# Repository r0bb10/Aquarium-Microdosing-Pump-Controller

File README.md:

# Aquarium-Microdosing-Pump-Controller
Software for an ESP8266 base aquarium micro-dosing pump. Controlled through a local webpage. Currently hard-coded to control a single pump, the hardware supports up to four. 

Required Libraries:
Adafruit I2C FRAM Library
Adafruit RTClib
ESPAsyncWebServer
ESPAsyncTCP
NTPClient
ESP8266TimerInterrupt
#Alepiro85 Changelog: ESP_EEPROM by j-watson

Also needed:
Setting up Arduino IDE to support uploading files to SPIFFS: https://randomnerdtutorials.com/install-esp8266-filesystem-uploader-arduino-ide/

Required Hardware:
MB85RC256V I2C FRAM. This is for saving configurations without constantly writing to internal memory to prevent excessive wearing. 
#Alepiro85 Changelog: from version 0.1A: Not necessary, it is possible to save parameters on EEPROM
DS3231 RTC. For keeping track of time if wifi is unavailable. 

Known Problems:
Need to redesign PCB to be smaller and cheaper. Software is hard-coded for a single pump. 
#Alepiro85 Changelog: from Version 0.1B: Software manages 4 pumps control

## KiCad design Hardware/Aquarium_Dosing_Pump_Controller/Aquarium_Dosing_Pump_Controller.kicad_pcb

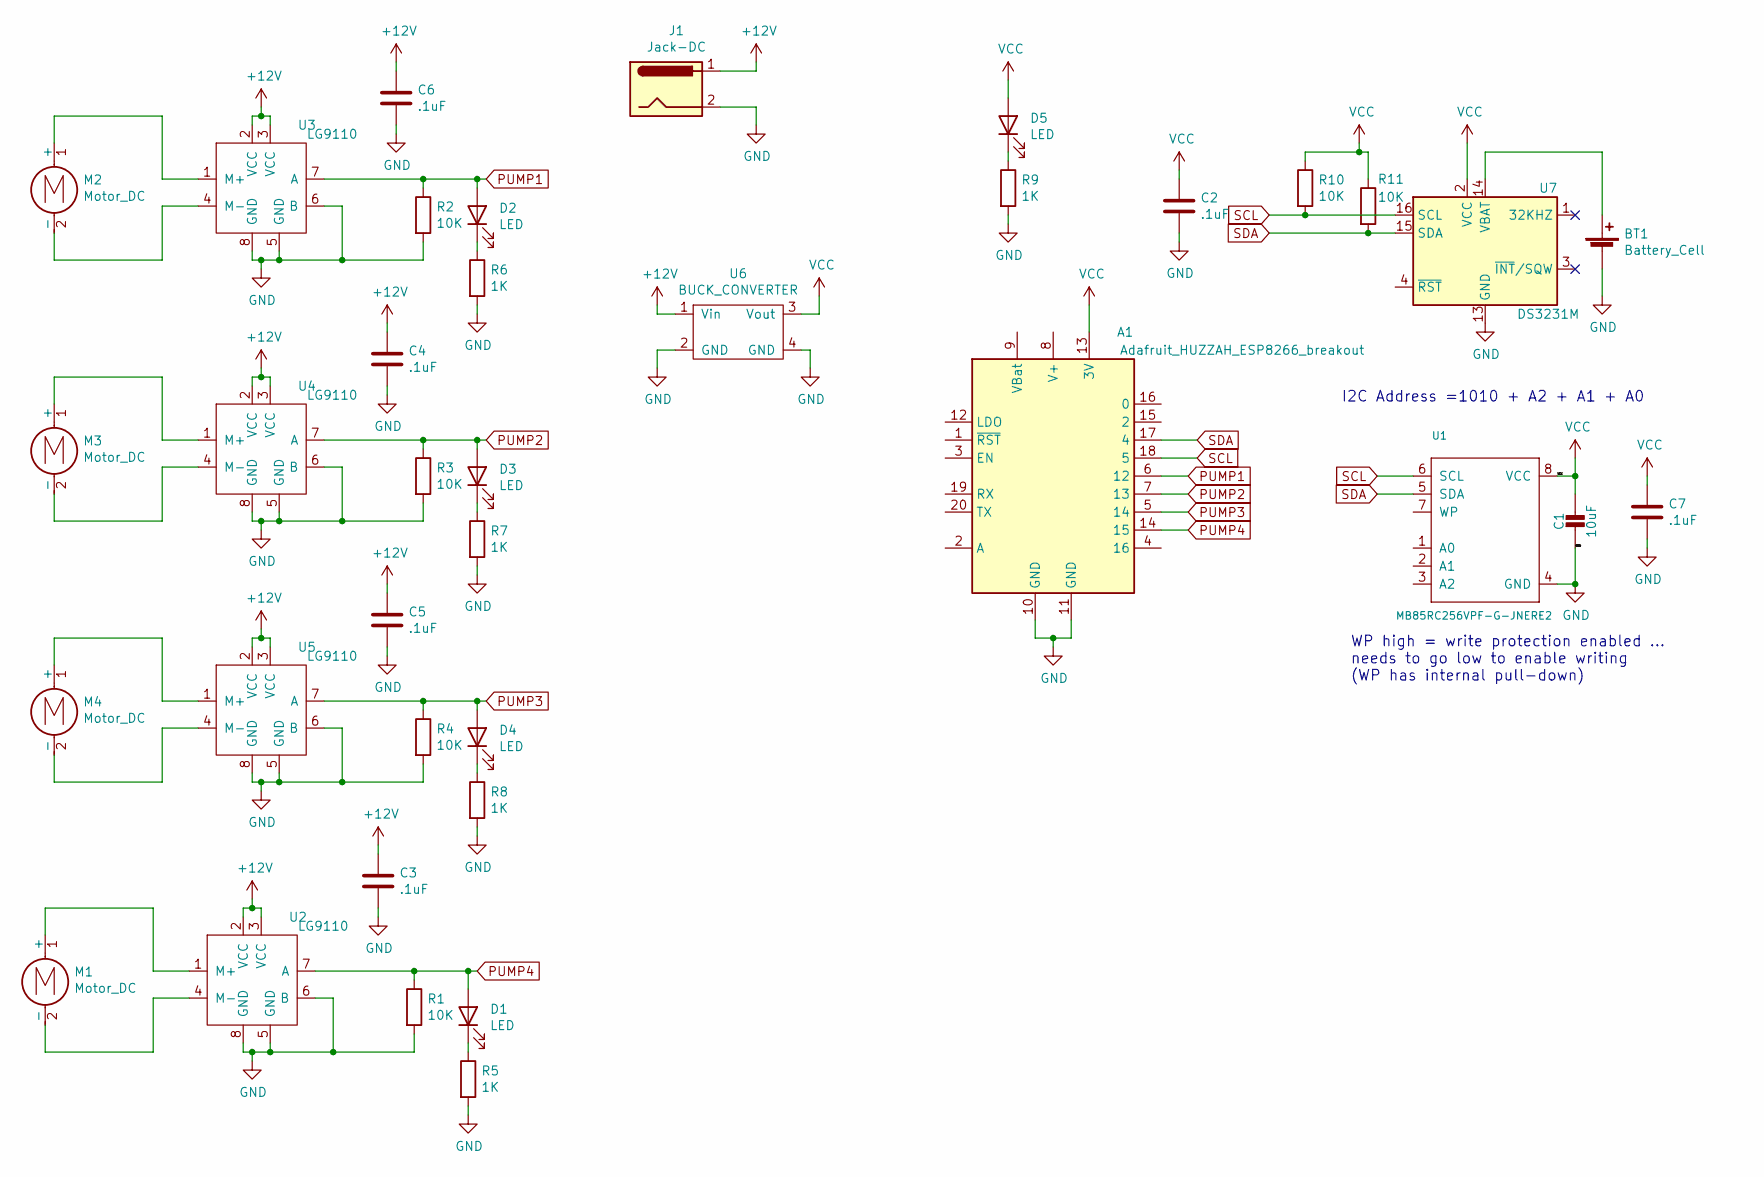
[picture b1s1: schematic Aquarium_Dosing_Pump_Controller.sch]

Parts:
A1: Adafruit_HUZZAH_ESP8266_breakout
BT1: Battery_Cell; CR1220
C1: 10uF; R_1206_3216Metric_Pad1.42x1.75mm_HandSolder
C2, C3, C4, C5, C6, C7: .1uF; R_1206_3216Metric_Pad1.42x1.75mm_HandSolder
D1, D2, D3, D4, D5: LED; LED_1206_3216Metric_Pad1.42x1.75mm_HandSolder
J1: Jack-DC; BarrelJack_Horizontal
M1, M2, M3, M4: Motor_DC; PinHeader_1x02_P2.54mm_Vertical
R1, R2, R3, R4, R10, R11: 10K; R_0603_1608Metric_Pad1.05x0.95mm_HandSolder
R5, R6, R7, R8, R9: 1K; R_0603_1608Metric_Pad1.05x0.95mm_HandSolder
U1: MB85RC256VPF-G-JNERE2; SOIJ-8_5.3x5.3mm_P1.27mm
U2, U3, U4, U5: LG9110; DIP-8_W7.62mm_LongPads
U6: BUCK_CONVERTER; Boost_Footprint
U7: DS3231M; SOIC-16W_7.5x10.3mm_P1.27mm

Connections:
+12V: C3.1, C4.1, C5.1, C6.1, J1.1, U2.2 (VCC), U2.3 (VCC), U3.2 (VCC), U3.3 (VCC), U4.2 (VCC), U4.3 (VCC), U5.2 (VCC), U5.3 (VCC), U6.1 (Vin)
GND: A1.10 (GND), A1.11 (GND), BT1.2 (-), C1.2, C2.2, C3.2, C4.2, C5.2, C6.2, C7.2, J1.2, R1.2, R2.2, R3.2, R4.2, R5.2, R6.2, R7.2, R8.2, R9.2, U1.4 (GND), U2.5 (GND), U2.6 (B), U2.8 (GND), U3.5 (GND), U3.6 (B), U3.8 (GND), U4.5 (GND), U4.6 (B), U4.8 (GND), U5.5 (GND), U5.6 (B), U5.8 (GND), U6.2 (GND), U6.4 (GND), U7.5 (GND), U7.6 (GND), U7.7 (GND), U7.8 (GND), U7.9 (GND), U7.10 (GND), U7.11 (GND), U7.12 (GND), U7.13 (GND)
unnamed: BT1.1 (+), U7.14 (VBAT)
unnamed: D1.1 (K), R5.1
unnamed: D2.1 (K), R6.1
unnamed: D3.1 (K), R7.1
unnamed: D4.1 (K), R8.1
unnamed: D5.1 (K), R9.1
unnamed: M1.1 (+), U2.1 (M+)
unnamed: M1.2 (-), U2.4 (M-)
unnamed: M2.1 (+), U3.1 (M+)
unnamed: M2.2 (-), U3.4 (M-)
unnamed: M3.1 (+), U4.1 (M+)
unnamed: M3.2 (-), U4.4 (M-)
unnamed: M4.1 (+), U5.1 (M+)
unnamed: M4.2 (-), U5.4 (M-)
PUMP1: A1.6 (12), D2.2 (A), R2.1, U3.7 (A)
PUMP2: A1.7 (13), D3.2 (A), R3.1, U4.7 (A)
PUMP3: A1.5 (14), D4.2 (A), R4.1, U5.7 (A)
PUMP4: A1.14 (15), D1.2 (A), R1.1, U2.7 (A)
SCL: A1.18 (5), R10.2, U1.6 (SCL), U7.16 (SCL)
SDA: A1.17 (4), R11.2, U1.5 (SDA), U7.15 (SDA)
VCC: A1.13 (3V), C1.1, C2.1, C7.1, D5.2 (A), R10.1, R11.1, U1.8 (VCC), U6.3 (Vout), U7.2 (VCC)

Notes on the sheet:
I2C Address =1010 + A2 + A1 + A0
WP high = write protection enabled ... needs to go low to enable writing~ (WP has internal pull-down)

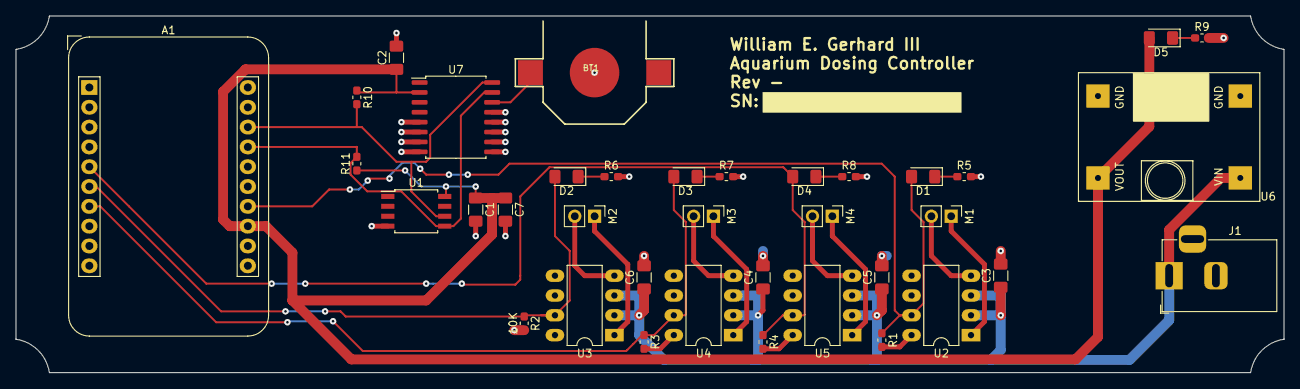
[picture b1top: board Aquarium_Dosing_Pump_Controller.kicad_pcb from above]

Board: 2 copper layers, 162.6 x 45.7 mm, 37 parts (0 on the bottom side), 23 nets.

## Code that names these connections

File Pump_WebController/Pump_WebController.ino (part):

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#define SETMEMADD 1000

// Set PUMP GPIO
const int gpio_PUMP1 = 12;
const int gpio_PUMP2 = 13;
const int gpio_PUMP3 = 14;
const int gpio_PUMP4 = 15;
const int pinReset = 16;
const int pinButton = 0;

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    EEPROM.begin(EEPROM_SIZE);
  #endif

  pinMode(gpio_PUMP1, OUTPUT);
  digitalWrite(gpio_PUMP1, LOW);
  pinMode(gpio_PUMP2, OUTPUT);
  digitalWrite(gpio_PUMP2, LOW);
  pinMode(gpio_PUMP3, OUTPUT);
  digitalWrite(gpio_PUMP3, LOW);
  pinMode(gpio_PUMP4, OUTPUT);
  digitalWrite(gpio_PUMP4, LOW);  

  WiFiManager wifiManager;
  wifiManager.setAPCallback(configModeCallback);
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    Serial.println(F("Can't set ITimer correctly. Select another frequency or interval"));
  }
  
  pump1 = loadPump(P1MEMADD,gpio_PUMP1);
  pump2 = loadPump(P2MEMADD,gpio_PUMP2);
  pump3 = loadPump(P3MEMADD,gpio_PUMP3);
  pump4 = loadPump(P4MEMADD,gpio_PUMP4);
  
  #ifdef EXT_MEMORY
    fram.read(SETMEMADD, tempSettings);
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  server.on("/cal1on", HTTP_GET, [] (AsyncWebServerRequest * request)
  {
    pump1.programEnable = false;
    digitalWrite(pump1.motor_GPIO, HIGH);
    startMillis = millis();
    #ifdef DEBUG
      Serial.println("ON");
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  server.on("/cal2on", HTTP_GET, [] (AsyncWebServerRequest * request)
  {
    pump2.programEnable = false;
    digitalWrite(pump2.motor_GPIO, HIGH);
    startMillis = millis();
    request->send(SPIFFS, "/index.html", String(), false);
  });
  server.on("/cal3on", HTTP_GET, [] (AsyncWebServerRequest * request)
  {
    pump3.programEnable = false;
    digitalWrite(pump3.motor_GPIO, HIGH);
    startMillis = millis();
    request->send(SPIFFS, "/index.html", String(), false);
  });
  server.on("/cal4on", HTTP_GET, [] (AsyncWebServerRequest * request)
  {
    pump4.programEnable = false;
    digitalWrite(pump4.motor_GPIO, HIGH);
    startMillis = millis();
    request->send(SPIFFS, "/index.html", String(), false);
  });
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  server.on("/cal1off", HTTP_GET, [] (AsyncWebServerRequest * request)
  {
    pump1.programEnable = true;
    digitalWrite(pump1.motor_GPIO, LOW);
    stopMillis = millis();
    pump1.CAL_pumpmS = (stopMillis - startMillis);
    Serial.println(pump1.CAL_pumpmS);
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  server.on("/cal2off", HTTP_GET, [] (AsyncWebServerRequest * request)
  {
    pump2.programEnable = true;
    digitalWrite(pump2.motor_GPIO, LOW);
    stopMillis = millis();
    pump2.CAL_pumpmS = (stopMillis - startMillis);
    Serial.println(pump2.CAL_pumpmS);
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  server.on("/cal3off", HTTP_GET, [] (AsyncWebServerRequest * request)
  {
    pump3.programEnable = true;
    digitalWrite(pump3.motor_GPIO, LOW);
    stopMillis = millis();
    pump3.CAL_pumpmS = (stopMillis - startMillis);
    Serial.println(pump3.CAL_pumpmS);
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  server.on("/cal4off", HTTP_GET, [] (AsyncWebServerRequest * request)
  {
    pump4.programEnable = true;
    digitalWrite(pump4.motor_GPIO, LOW);
    stopMillis = millis();
    pump4.CAL_pumpmS = (stopMillis - startMillis);
    Serial.println(pump4.CAL_pumpmS);
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  server.on("/on1", HTTP_GET, [] (AsyncWebServerRequest * request)
  {
    pump1.programEnable = false;
    digitalWrite(pump1.motor_GPIO, HIGH);
    request->send(SPIFFS, "/index.html", String(), false);
  });
  server.on("/on2", HTTP_GET, [] (AsyncWebServerRequest * request)
  {
    pump2.programEnable = false;
    digitalWrite(pump2.motor_GPIO, HIGH);
    request->send(SPIFFS, "/index.html", String(), false);
  });
  server.on("/on3", HTTP_GET, [] (AsyncWebServerRequest * request)
  {
    pump3.programEnable = false;
    digitalWrite(pump3.motor_GPIO, HIGH);
    request->send(SPIFFS, "/index.html", String(), false);
  });
  server.on("/on4", HTTP_GET, [] (AsyncWebServerRequest * request)
  {
    pump4.programEnable = false;
    digitalWrite(pump4.motor_GPIO, HIGH);
    request->send(SPIFFS, "/index.html", String(), false);
  });

  server.on("/off1", HTTP_GET, [] (AsyncWebServerRequest * request)
  {
    digitalWrite(pump1.motor_GPIO, LOW);
    pump1.programEnable = true;
    request->send(SPIFFS, "/index.html", String(), false);
  });
  server.on("/off2", HTTP_GET, [] (AsyncWebServerRequest * request)
  {
    digitalWrite(pump2.motor_GPIO, LOW);
    pump2.programEnable = true;
    request->send(SPIFFS, "/index.html", String(), false);
  });
  server.on("/off3", HTTP_GET, [] (AsyncWebServerRequest * request)
  {
    digitalWrite(pump3.motor_GPIO, LOW);
    pump3.programEnable = true;
    request->send(SPIFFS, "/index.html", String(), false);
  });
  server.on("/off4", HTTP_GET, [] (AsyncWebServerRequest * request)
  {
    digitalWrite(pump4.motor_GPIO, LOW);
    pump4.programEnable = true;
    request->send(SPIFFS, "/index.html", String(), false);
  });
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
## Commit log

2021-05-27 Intial Commit
    Adds current working version of code. Supports only 1 dosing pump.
2021-05-27 Update README.md
    Added more details and required libraries.
2021-05-27 Added hardware files
    Added the Kicad files for the hardware.
2021-05-27 Added Schematic PDF of Hardware
2021-06-17 Updated time sync to only use RTC
    Internal timer will only be updated from I2C rtc module, and RTC module will be updated from online time server when valid. This fixed a bug where sometimes the controller would have the incorrect ti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
2023-02-03 first compiling version with ifdef EXT_MEMORY
2023-02-04 EEPROM management added, TODOs removed
2023-02-04 write many times bug verifing, little code indentation improvement
2023-02-04 4 pumps management, indentation improvement
2023-02-05 RTC brutally excluded, serial debug for multiple writing
2023-02-05 multiple memory write solved, set table in status web page
2023-02-06 Update index.html
    pump management in table design
2023-02-06 css and html graphic improvement
2023-02-07 Update javascript.js
    This JS is completely unworking, need to review it heavily
2023-02-07 Update index.html
    Have to define pages and object IDs and create functions in JS file
2023-02-07 EEPROM test and debug strings print by DEBUG declaration
2023-02-08 EEPROM reading inserted
2023-02-08 Removed hardcoded WiFi and implemented WiFiManager
2023-02-08 Code cleanup, add mDNS, renamed to MicroDoser
2023-02-08 WIP FactoryReset routine.
2023-02-08 write and read of the 4 pumps structures in eeprom
2023-02-09 struct corrected and check EEPROM from Bool to Char
2023-02-09 almost connect ino and html variables, some js problem on 2nd value change
2023-02-10 internal RTC implemented and work well, lot of disconnections, why?
2023-02-10 minr
2023-02-12 calibration timers and buttons fixed
2023-02-13 Update Pump_WebController.ino
    get values from webpage test
2023-02-13 Update javascript.js
    save1 func test
2023-02-16 minor corrections
2023-02-21 commit 01
2023-02-21 read value from url
2023-02-25 correctly write data from programs, calibration, dst and reply
2023-03-11 date_now now is working properly, add loop for increase next doses
